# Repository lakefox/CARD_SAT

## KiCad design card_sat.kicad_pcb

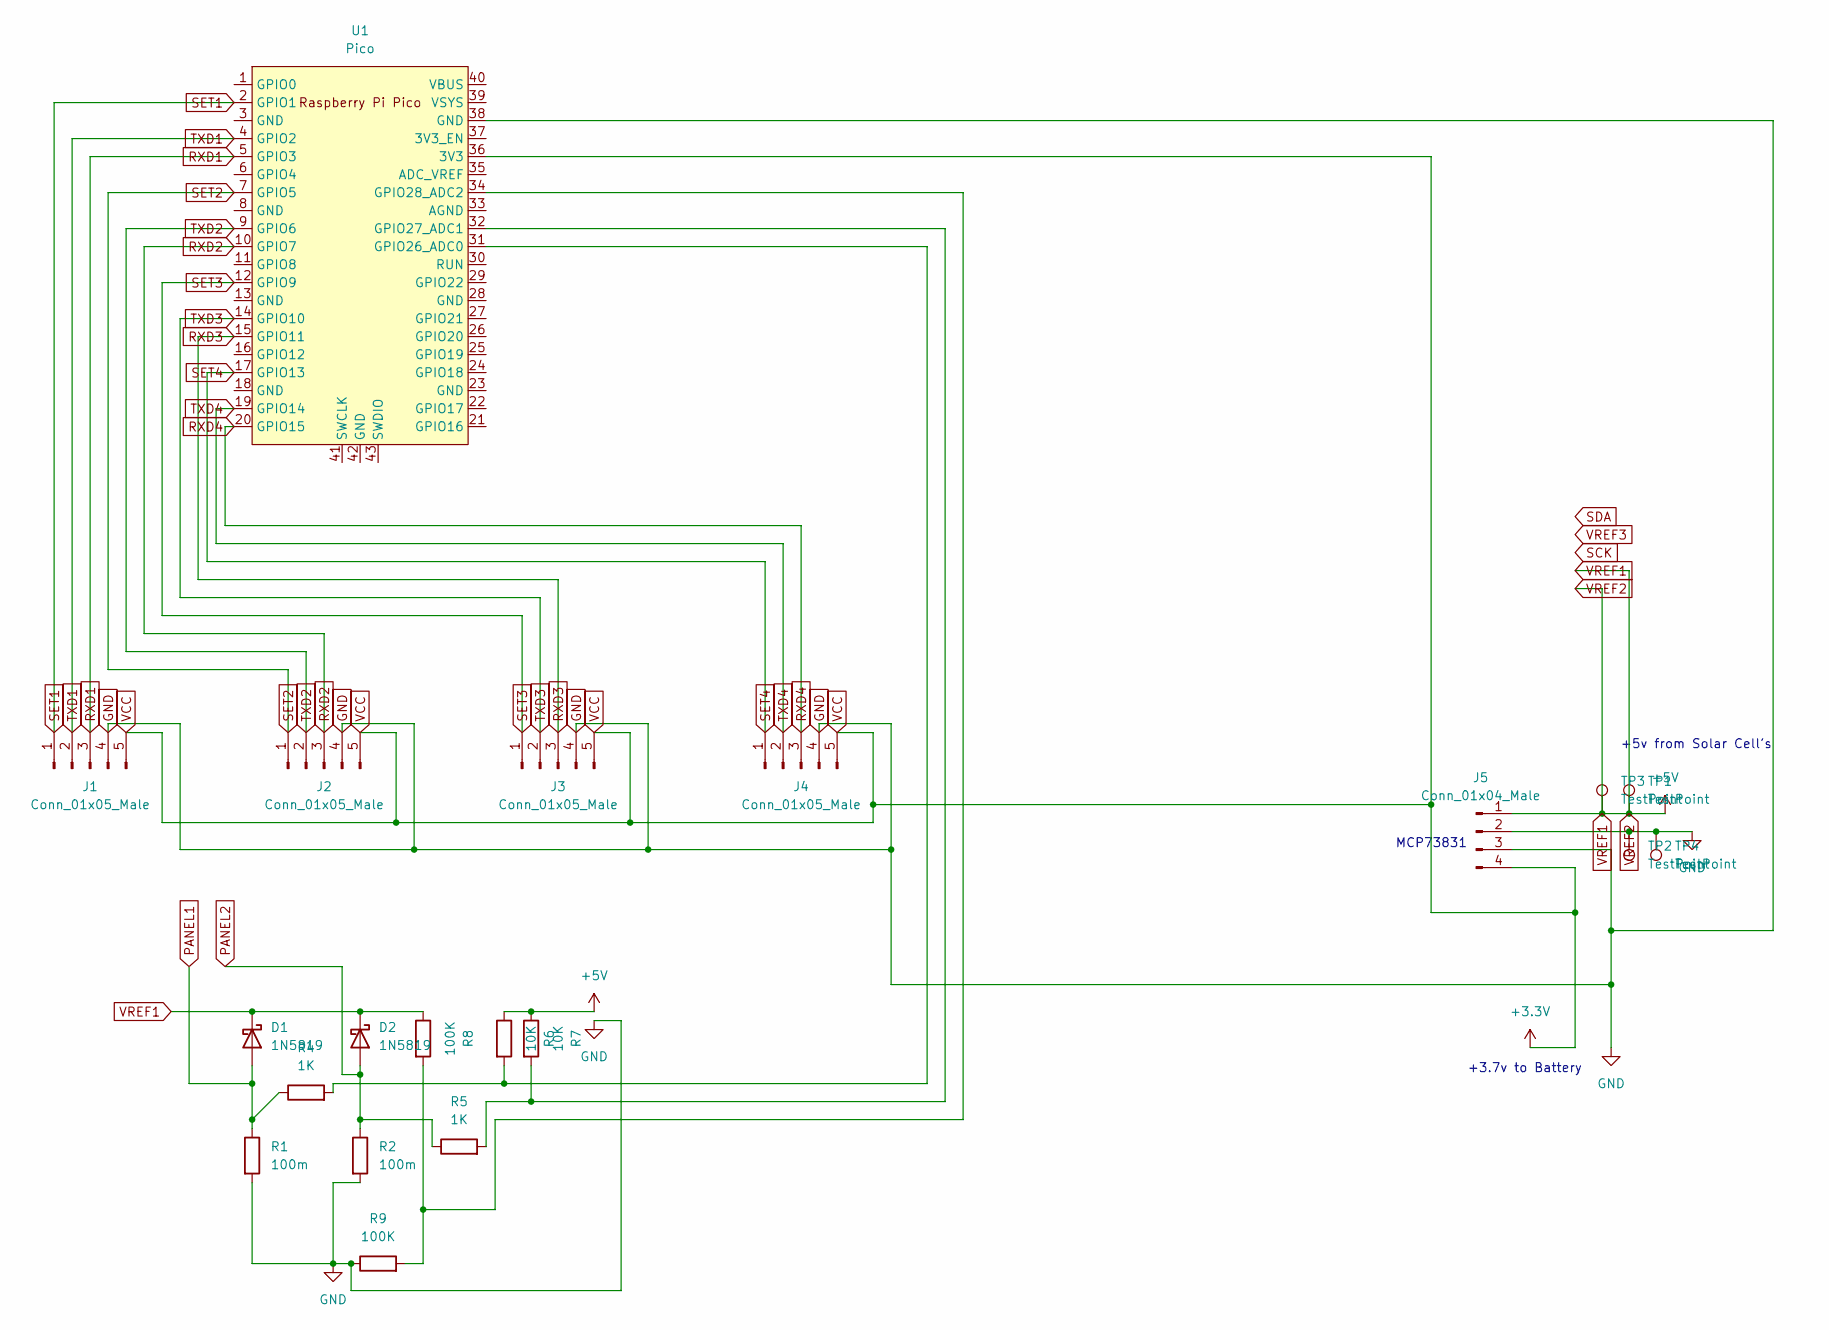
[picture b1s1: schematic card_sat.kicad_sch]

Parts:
D1, D2: 1N5819; D_DO-41_SOD81_P10.16mm_Horizontal
J1, J2, J3, J4: Conn_01x05_Male; PinHeader_1x05_P2.54mm_Vertical
J5: Conn_01x04_Male; PinHeader_1x04_P2.54mm_Vertical
R1, R2: 100m; R_Axial_DIN0204_L3.6mm_D1.6mm_P5.08mm_Horizontal
R4, R5: 1K; R_Axial_DIN0204_L3.6mm_D1.6mm_P5.08mm_Horizontal
R6, R7: 10K; R_Axial_DIN0204_L3.6mm_D1.6mm_P5.08mm_Horizontal
R8, R9: 100K; R_Axial_DIN0204_L3.6mm_D1.6mm_P5.08mm_Horizontal
TP1, TP2, TP3, TP4: TestPoint; TestPoint_Pad_2.5x2.5mm
U1: Pico; RPi_Pico_SMD_TH

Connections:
GND: J1.4, J2.4, J3.4, J4.4, J5.2, J5.3, R1.2, R2.2, R9.1, TP2.1, TP4.1, U1.38 (GND)
unnamed: R4.2, R6.2, U1.31 (GPIO26_ADC0)
unnamed: R5.2, R7.2, U1.32 (GPIO27_ADC1)
unnamed: R8.2, R9.2, U1.34 (GPIO28_ADC2)
PANEL1: D1.2 (A), R1.1, R4.1
PANEL2: D2.2 (A), R2.1, R5.1
RXD1: J1.3, U1.5 (GPIO3)
RXD2: J2.3, U1.10 (GPIO7)
RXD3: J3.3, U1.15 (GPIO11)
RXD4: J4.3, U1.20 (GPIO15)
SET1: J1.1, U1.2 (GPIO1)
SET2: J2.1, U1.7 (GPIO5)
SET3: J3.1, U1.12 (GPIO9)
SET4: J4.1, U1.17 (GPIO13)
TXD1: J1.2, U1.4 (GPIO2)
TXD2: J2.2, U1.9 (GPIO6)
TXD3: J3.2, U1.14 (GPIO10)
TXD4: J4.2, U1.19 (GPIO14)
VCC: J1.5, J2.5, J3.5, J4.5, J5.4, U1.36 (3V3)
VREF1: D1.1 (K), D2.1 (K), J5.1, R6.1, R7.1, R8.1, TP1.1, TP3.1

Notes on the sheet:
+3.7v to Battery
+5v from Solar Cell's
MCP73831

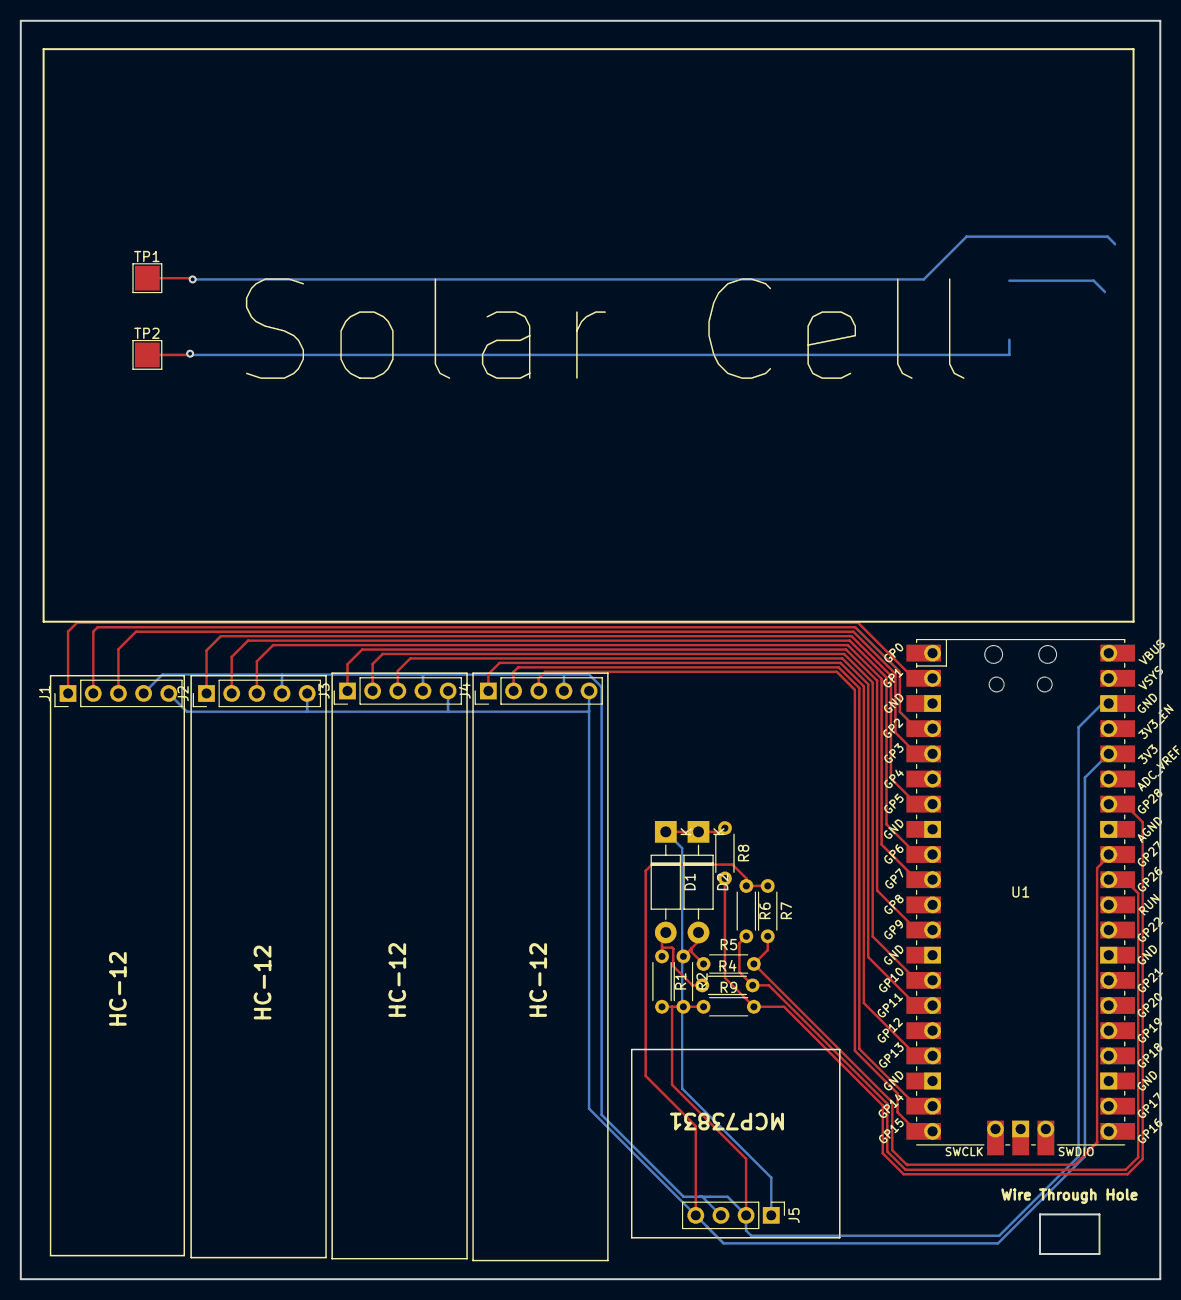
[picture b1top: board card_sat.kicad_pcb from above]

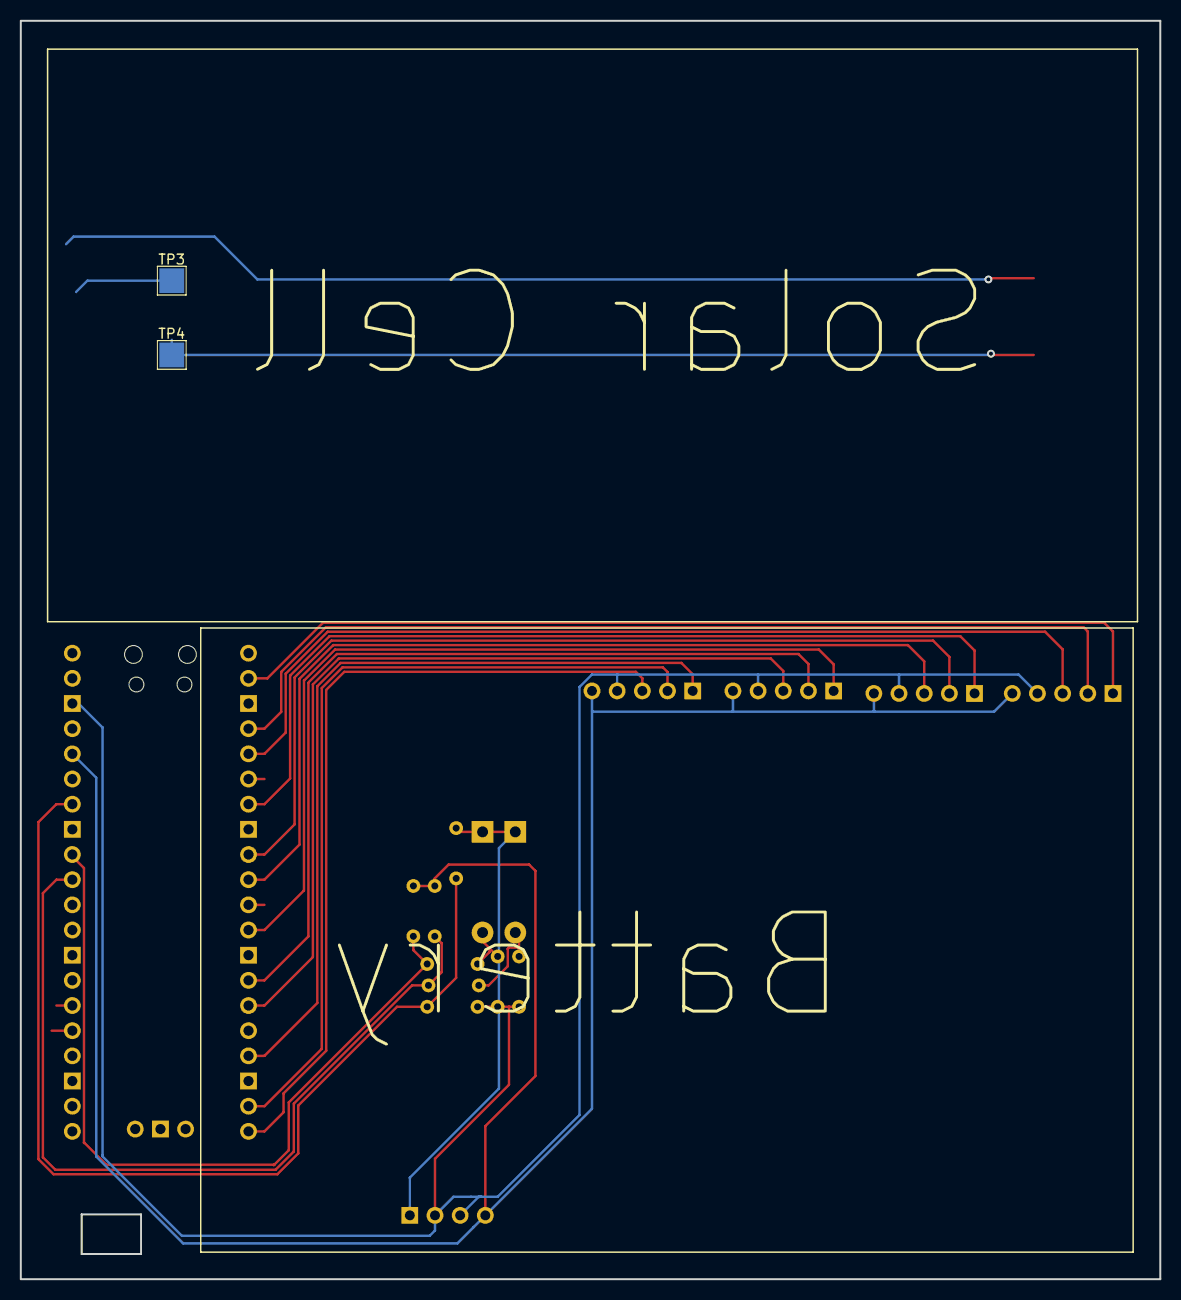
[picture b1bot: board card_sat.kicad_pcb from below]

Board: 2 copper layers, 115.0 x 127.0 mm, 20 parts (2 on the bottom side), 20 nets.

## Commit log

2022-06-30 Upload
2022-07-01 OTHER function half written
2022-07-02 save
2022-07-03 changed schematic to use pico
2022-07-05 redoing all the code
2022-07-06 switched to python
2022-07-06 building
2022-07-07 refactoring
2022-07-07 changed the memory clean up
2022-07-08 added artic controller
2022-07-08 adjusted user deletion and line termination logic
2022-07-08 Added SETID
2022-07-10 debugging still :(
2022-07-11 got uart working and rxing messages
2022-07-12 shes getting there
2022-07-16 still working
